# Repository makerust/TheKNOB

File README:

# TheKNOB

# First Time Setup for development
`git pull --recurse-submodules`
Sketch > Include Library > Add .ZIP Library
Navigate to the ESP library in thirdparty

In:
File > Preference > Additional Boards Manager URLS
Add:
`https://dl.espressif.com/dl/package_esp32_index.json, http://arduino.esp8266.com/stable/package_esp8266com_index.json`
Select:
Tools > Board > Board Manager
Search: ESP32
Install Board Library
Select:
Tools > Board > Board Manager > ESP32 Dev Module

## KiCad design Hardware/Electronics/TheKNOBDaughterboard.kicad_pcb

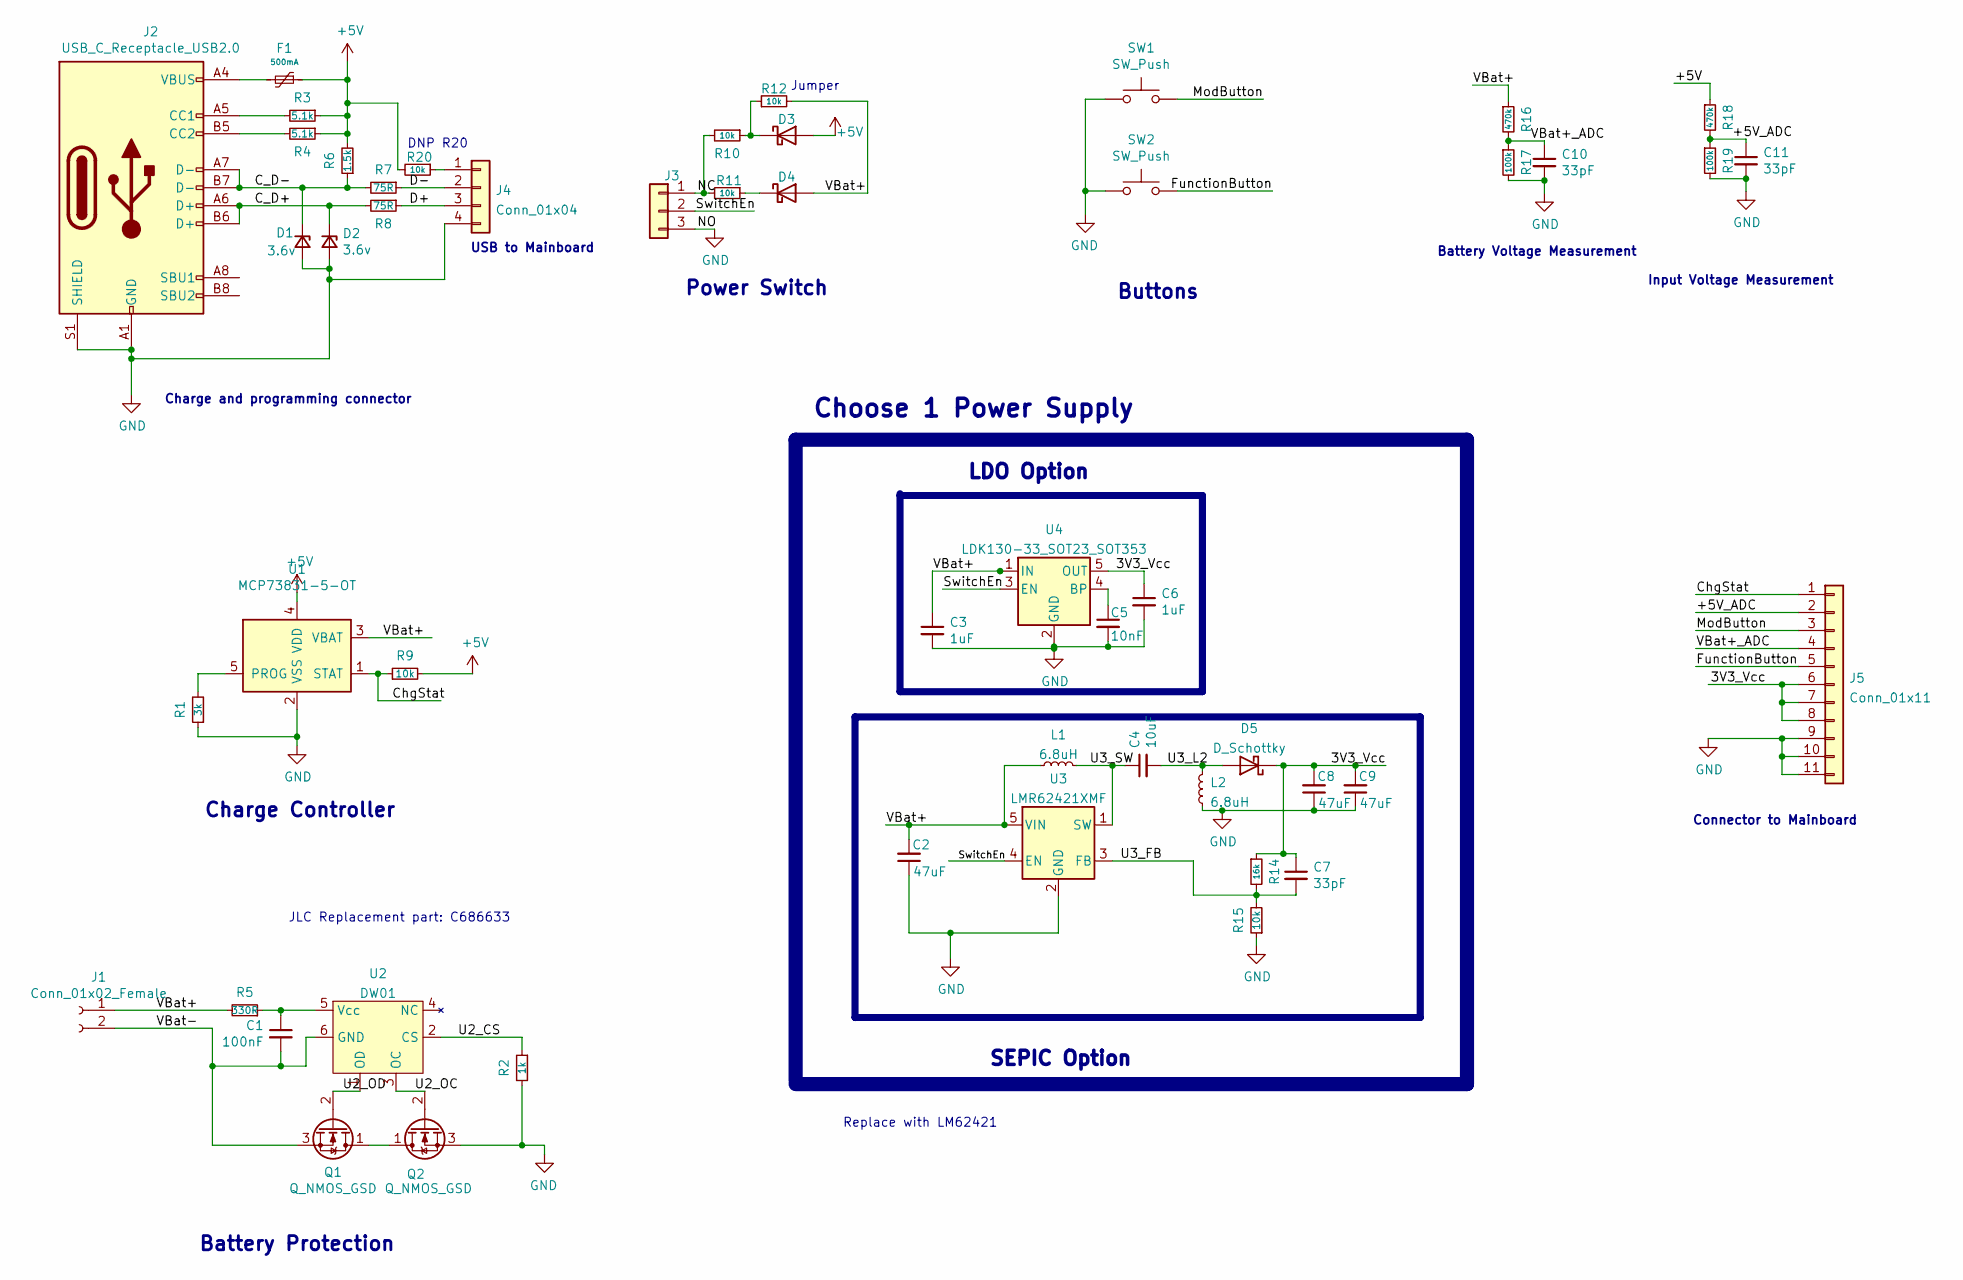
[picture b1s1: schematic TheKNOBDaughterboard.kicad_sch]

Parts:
C1: 100nF; C_0603_1608Metric
C2, C8, C9: 47uF; C_1206_3216Metric; MFR_PN C3216X5R1A336MTJ00N
C3, C6: 1uF; C_0603_1608Metric
C4: 10uF; C_0603_1608Metric
C5: 10nF; C_0603_1608Metric
C7, C10, C11: 33pF; C_0603_1608Metric
D1, D2: 3.6v; D_SOD-323_HandSoldering; MFR_PN BZT52-B3V6S_R1_00001
D3, D4, D5: D_Schottky; D_SOD-123; MFR_PN 1N5819HW
F1: 500mA; Fuse_1206_3216Metric; MFR_PN nSMD025
J1: Conn_01x02_Female; JST_PH_S2B-PH-SM4-TB_1x02-1MP_P2.00mm_Horizontal
J2: USB_C_Receptacle_USB2.0; USB_C_Receptacle_HRO_TYPE-C-31-M-12; MFR_PN TYPE-C-31-M-12
J3: Conn_01x03; JST_EH_B3B-EH-A_1x03_P2.50mm_Vertical
J4: Conn_01x04; JST_EH_B4B-EH-A_1x04_P2.50mm_Vertical
J5: Conn_01x11; JST_EH_B11B-EH-A_1x11_P2.50mm_Vertical
L1, L2: 6.8uH; L_1210_3225Metric; MFR_PN LBC3225T6R8MR
Q1, Q2: Q_NMOS_GSD; SOT-23; MFR_PN AO3400A
R1: 3k; R_0603_1608Metric
R2: 1k; R_0603_1608Metric
R3, R4: 5.1k; R_0603_1608Metric
R5: 330R; R_0603_1608Metric
R6: 1.5k; R_0603_1608Metric
R7, R8: 75R; R_0603_1608Metric
R9, R10, R11, R12, R15, R20: 10k; R_0603_1608Metric
R14: 16k; R_0603_1608Metric
R16, R18: 470k; R_0603_1608Metric
R17, R19: 100k; R_0603_1608Metric
SW1, SW2: SW_Push; ALPS_SKPM
U1: MCP73831-5-OT; SOT-23-5
U2: DW01; SOT-23-6
U3: LMR62421XMF; SOT-23-5
U4: LDK130-33_SOT23_SOT353; SOT-353_SC-70-5

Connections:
+5V: D3.2 (A), F1.1, R3.1, R4.1, R6.2, R9.2, R18.1, R20.2, U1.4 (VDD)
/3V3_Vcc: C6.1, C7.1, C8.2, C9.2, D5.1 (K), J5.6, J5.7, J5.8, R14.1, U4.5 (OUT)
/+5V_ADC: C11.1, J5.2, R18.2, R19.1
/C_D+: D2.1 (K), J2.A6 (D+), J2.B6 (D+), R8.2
/C_D-: D1.1 (K), J2.A7 (D-), J2.B7 (D-), R6.1, R7.2
/ChgStat: J5.1, R9.1, U1.1 (STAT)
/D+: J4.3, R8.1
/D-: J4.2, R7.1
/FunctionButton: J5.5, SW2.1
/ModButton: J5.3, SW1.1
/NC: J3.1, R10.2, R11.2
/SwitchEn: J3.2, U3.4 (EN), U4.3 (EN)
/U2_CS: R2.1, U2.2 (CS)
/U2_OC: Q2.2 (G), U2.3 (OC)
/U2_OD: Q1.2 (G), U2.1 (OD)
/U3_FB: C7.2, R14.2, R15.2, U3.3 (FB)
/U3_L2: C4.2, D5.2 (A), L2.2
/U3_SW: C4.1, L1.2, U3.1 (SW)
/VBat+: C2.2, C3.1, D4.2 (A), J1.1, J1.MP, L1.1, R5.2, R12.2, R16.1, U1.3 (VBAT), U3.5 (VIN), U4.1 (IN)
/VBat+_ADC: C10.1, J5.4, R16.2, R17.1
/VBat-: C1.2, J1.2, Q1.3 (S), U2.6 (GND)
GND: C2.1, C3.2, C5.2, C6.2, C8.1, C9.1, C10.2, C11.2, D1.2 (A), D2.2 (A), J2.A1 (GND), J2.A12 (GND), J2.B1 (GND), J2.B12 (GND), J2.S1 (SHIELD), J3.3, J4.4, J5.9, J5.10, J5.11, L2.1, Q2.3 (S), R1.1, R2.2, R15.1, R17.2, R19.2, SW1.2, SW2.2, U1.2 (VSS), U3.2 (GND), U4.2 (GND)
unnamed: C1.1, R5.1, U2.5 (Vcc)
unnamed: C5.1, U4.4 (BP)
unnamed: D3.1 (K), R10.1, R12.1
unnamed: D4.1 (K), R11.1
unnamed: F1.2, J2.A4 (VBUS), J2.A9 (VBUS), J2.B4 (VBUS), J2.B9 (VBUS)
unnamed: J2.A5 (CC1), R3.2
unnamed: J2.B5 (CC2), R4.2
unnamed: J4.1, R20.1
unnamed: Q1.1 (D), Q2.1 (D)
unnamed: R1.2, U1.5 (PROG)

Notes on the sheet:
USB to Mainboard
LDO Option
Connector to Mainboard
Charge and programming connector
Power Switch
Input Voltage Measurement
Replace with LM62421
Charge Controller
Battery Protection
DNP R20
Jumper
Choose 1 Power Supply
SEPIC Option
JLC Replacement part: C686633
Buttons
Battery Voltage Measurement

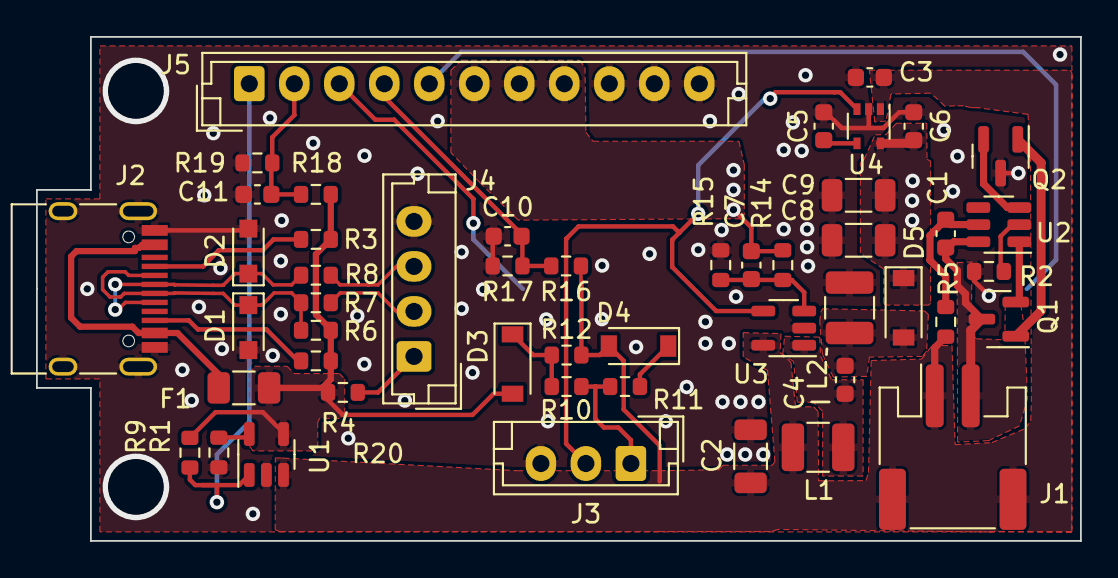
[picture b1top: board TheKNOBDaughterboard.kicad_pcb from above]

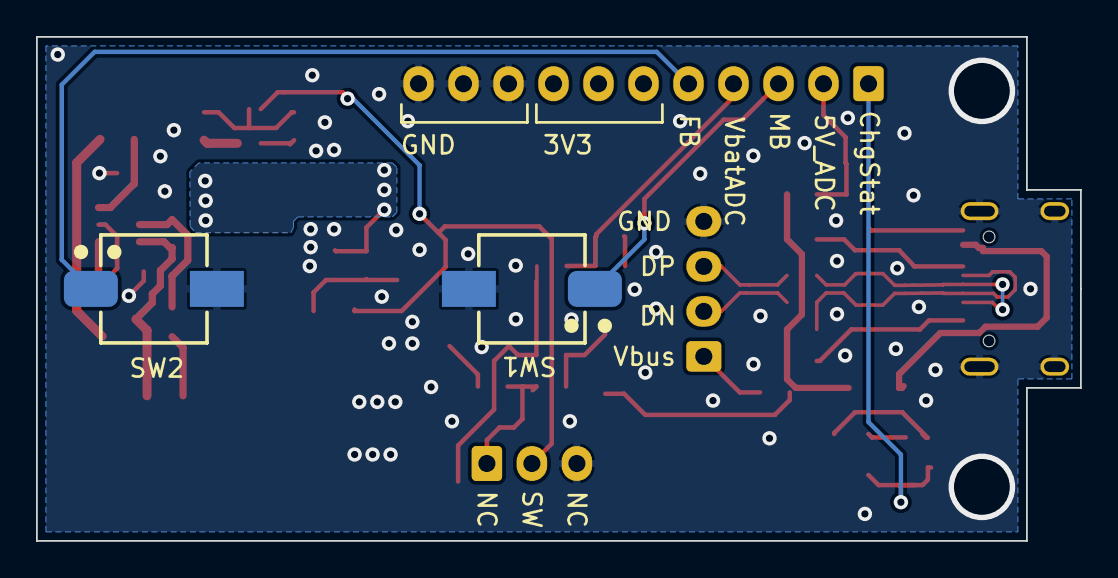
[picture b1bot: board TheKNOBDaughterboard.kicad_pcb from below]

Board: 2 copper layers, 58.0 x 28.0 mm, 51 parts (2 on the bottom side), 32 nets.

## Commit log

2021-09-30 Second attempt
2021-09-30 Simplified encoder code, split button ISR to own function
2021-09-30 new encoder code. doesn't work
2021-10-04 replaced noInterrupt() function with mutex and critical section
2021-10-04 cleaned
2021-10-04 note about libary version
2021-10-04 linked url of libary version
2021-10-06 changed pins, activated rr ff and Func fuctions. Add timeout stub
2021-10-06 see previous
2021-10-07 added sleep function
2021-10-15 fixes issue 1 with debug macro. Adds battery level set. Adds better wakeup handler.
2021-10-17 changed timeout to 5 minutes
2021-10-18 added first draft neopixel
2021-10-19 refactored a little bit
2021-12-21 minor changes
2021-12-21 added hardware folder containing electronics hardware design files, hardware stl files and hardware design files
2021-12-23 added Gerbers, Bom and Pick and place files.
2021-12-23 add 3d files, changes to sch and pcb
2021-12-23 add gitignore
2021-12-26 Batt Protection and SMPS chip changed due to chip shortage
2021-12-26 missed some files
2022-05-26 Changed LED colorspace to HSV so that brightness can be easily changed per housing material, added battery read buffer/average, added background color to flash and fuction to have orange background w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
2022-11-26 Add ESP32-BLE as submodule
2022-11-26 Add very basic readme
2022-11-28 Replaces manual critical section cleanup with RAII magic
2022-11-28 const all the things
2022-11-28 simplify charge lookup
2022-11-29 Replace mailbox with c++ Adds mailbox.hpp, removes definitions
